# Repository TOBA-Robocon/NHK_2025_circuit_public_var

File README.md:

# 前提(注意)
USB-CのD+,D-にCANを流す異端ゲキヤバ思想。
USBに規格外信号を流すなって人はブラウザバックを推奨。
著作権保護とかのために本番で使ったデータをちょっと改変してたりする。

# 各基板説明

## CAN_HUB_SMD
USB-CのCANバスを分岐するための基板。

付属のXT60に給電することで分岐先のUSB-Cの電源ラインに電源を供給できる。

電源を供給することで後述する「偽C610(C810)」を駆動させることができる。

本番で使った基板にはれな子のシルクが乗っているため、部内では「れな子」と呼ばれていた。

## CANはぶ
CAN_HUB_SMDの旧バージョン。

使ってるUSB-Cのコネクタが違う。

## GOD_DC_MD
強いモタドラ

定格:40V/60A

## Next_main_Control
メインの基板。

ESP32とF405RGTがついている。Dualshock4の値をESP32で受け取ってCANバスに流し散らかす。

Dualshock4の値を使って各機構の処理をし、4本のUSB-C_CANで各基板にデータを転送する。

ESP32で流すデータの種類とか規格は「ESP32」フォルダの中を参照のこと。

## mecanum_HUB
メカナムを動かしている基板

CAN*1、ロリコン*2(XAコネクタ5pin)、リミットスイッチ*2(XAコネクタ2pin)、電流センサ*2、「GOD_DC_MD」を刺すスロット*2,

メイン基板からのデューティー比と回転方向司令をCANで受けてメカナムを回す

## ガチ夫
ベル直道機構をPID制御する基板

定格:40V/20A

CAN*1、ロリコン*1(XAコネクタ5pin)、リミットスイッチ*1(PHコネクタ2pin)、電流センサ*1、モータードライバ*1ch

メイン基板から速度司令をCANで受けて定速度でベル直を回す。

## 偽C610(C810)
C610サイズのDCモータードライバ

定格:24V/5A

USB-Cから電源とCANを引ける

CAN*1、リミットスイッチ*1(PHコネクタ2pin)、モータードライバ*1ch

メイン基板からデューティー比と回転方向司令をCANで受けてモーターを回す。

基板をロボットに固定するのがめんどくさすぎる駄作。

# iocs
各基板に乗っているSTM32用の.iocファイル群

参考程度にCubeIDE等で使って、どうぞ。

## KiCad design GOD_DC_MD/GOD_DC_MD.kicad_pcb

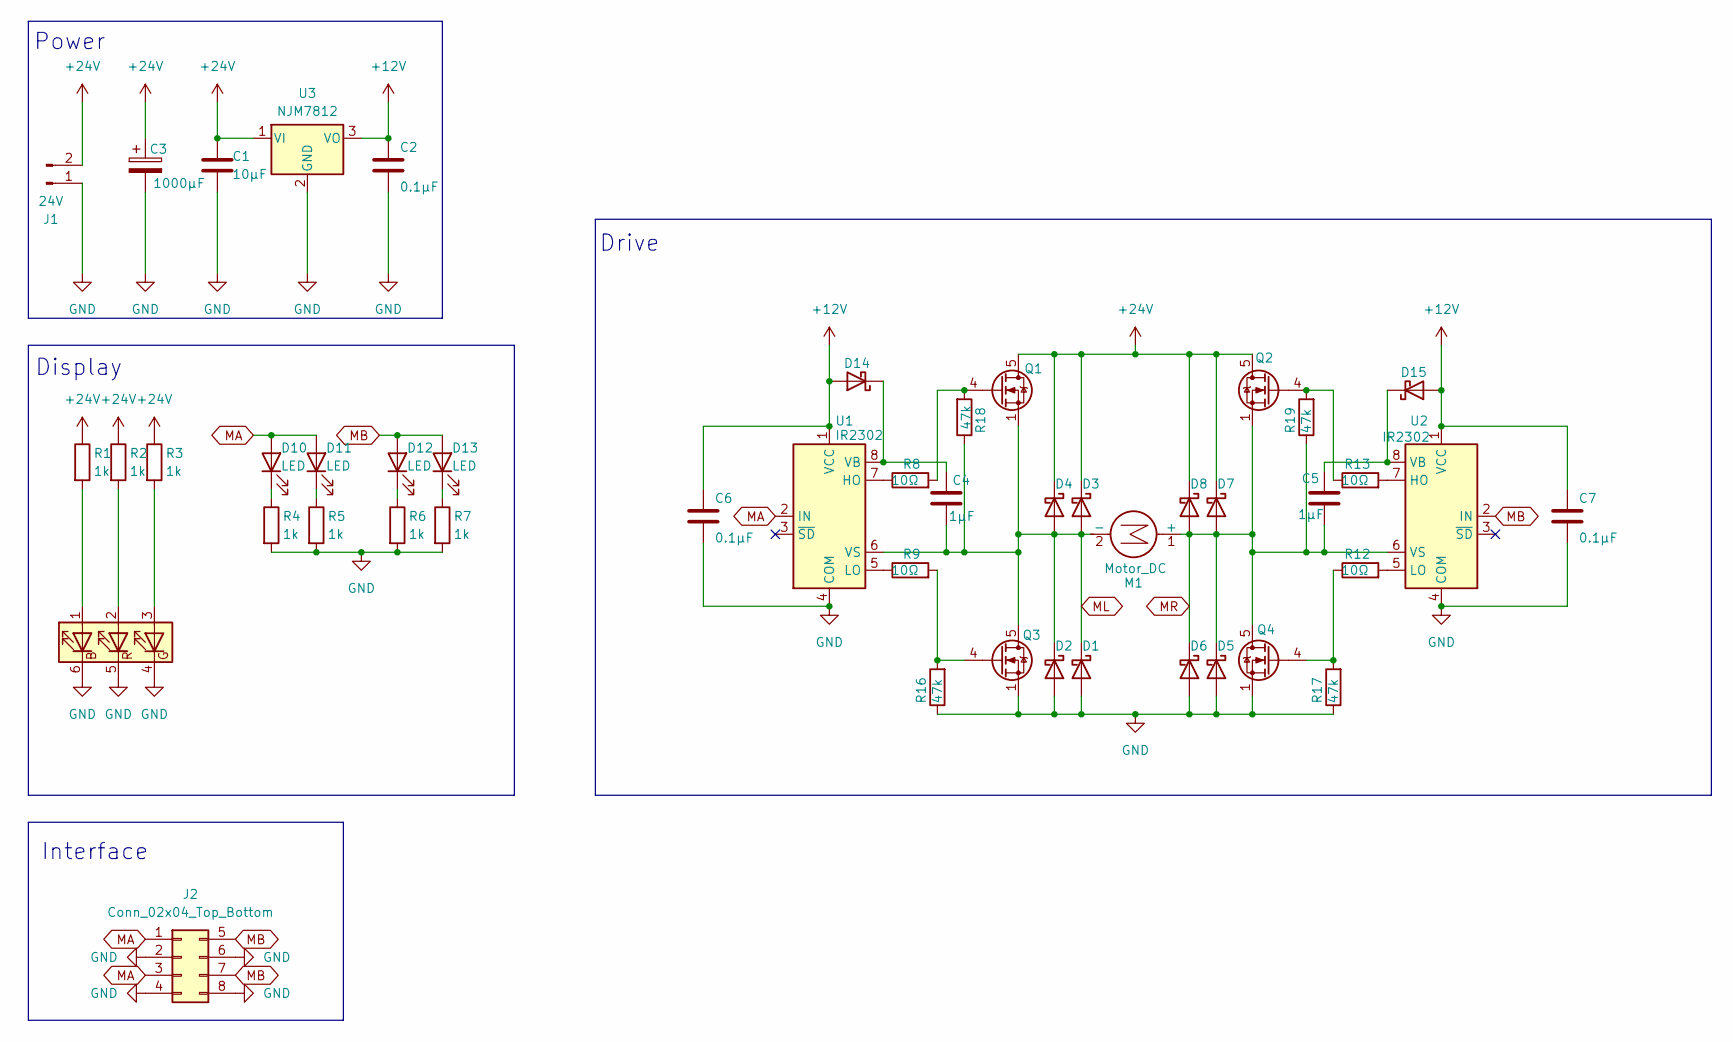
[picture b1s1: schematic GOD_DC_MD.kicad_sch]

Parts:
C1: 10μF; C_0603_1608Metric_Pad1.08x0.95mm_HandSolder
C2, C6, C7: 0.1μF; C_0603_1608Metric_Pad1.08x0.95mm_HandSolder
C3: 1000μF; CP_Radial_D10.0mm_P7.50mm
C4, C5: 1μF; C_0603_1608Metric_Pad1.08x0.95mm_HandSolder
D1, D2, D3, D4, D5, D6, D7, D8, D14, D15: SS14; D_SMA_Handsoldering
D9: SMLVN6RGB; LED_ROHM_SMLVN6
D10, D11, D12, D13: LED; LED_0603_1608Metric_Pad1.05x0.95mm_HandSolder
J1: 24V; AMASS_XT60PW-M_1x02_P7.20mm_Horizontal
J2: Conn_02x04_Top_Bottom; PinHeader_2x04_P2.54mm_Horizontal
M1: Motor_DC; AMASS_XT60PW-F_1x02_P7.20mm_Horizontal
Q1, Q2, Q3, Q4: BSC159N10LSFG; TDSON-8-1
R1, R2, R3, R4, R5, R6, R7: 1k; R_0603_1608Metric_Pad0.98x0.95mm_HandSolder
R8, R9, R12, R13: 10Ω; R_0603_1608Metric_Pad0.98x0.95mm_HandSolder
R16, R17, R18, R19: 47k; R_0603_1608Metric_Pad0.98x0.95mm_HandSolder
U1, U2: IR2302; SOIC-8_3.9x4.9mm_P1.27mm
U3: NJM7812; TO-252-2

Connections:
+12V: C2.1, C6.1, C7.1, D14.2 (A), D15.2 (A), U1.1 (VCC), U2.1 (VCC), U3.3 (VO)
+24V: C1.1, C3.1, D3.1 (K), D4.1 (K), D7.1 (K), D8.1 (K), J1.2, Q1.5 (D), Q2.5 (D), R1.1, R2.1, R3.1, U3.1 (VI)
GND: C1.2, C2.2, C3.2, C6.2, C7.2, D1.2 (A), D2.2 (A), D5.2 (A), D6.2 (A), D9.4 (GK), D9.5 (RK), D9.6 (BK), J1.1, J2.2, J2.4, J2.6, J2.8, Q3.1 (S), Q3.2 (S), Q3.3 (S), Q4.1 (S), Q4.2 (S), Q4.3 (S), R4.2, R5.2, R6.2, R7.2, R16.1, R17.1, U1.4 (COM), U2.4 (COM), U3.2 (GND)
MA: D10.2 (A), D11.2 (A), J2.1, J2.3, U1.2 (IN)
MB: D12.2 (A), D13.2 (A), J2.5, J2.7, U2.2 (IN)
ML: C4.2, D1.1 (K), D2.1 (K), D3.2 (A), D4.2 (A), M1.2 (-), Q1.1 (S), Q1.2 (S), Q1.3 (S), Q3.5 (D), R18.1, U1.6 (VS)
MR: C5.2, D5.1 (K), D6.1 (K), D7.2 (A), D8.2 (A), M1.1 (+), Q2.1 (S), Q2.2 (S), Q2.3 (S), Q4.5 (D), R19.1, U2.6 (VS)
unnamed: D9.1 (BA), R1.2
unnamed: D9.3 (GA), R3.2
unnamed: D9.2 (RA), R2.2
unnamed: D10.1 (K), R4.1
unnamed: D11.1 (K), R5.1
unnamed: D12.1 (K), R6.1
unnamed: D13.1 (K), R7.1
unnamed: C4.1, D14.1 (K), U1.8 (VB)
unnamed: C5.1, D15.1 (K), U2.8 (VB)
unnamed: Q1.4 (G), R8.2, R18.2
unnamed: Q2.4 (G), R13.1, R19.2
unnamed: Q3.4 (G), R9.2, R16.2
unnamed: Q4.4 (G), R12.1, R17.2
unnamed: R8.1, U1.7 (HO)
unnamed: R9.1, U1.5 (LO)
unnamed: R13.2, U2.7 (HO)
unnamed: R12.2, U2.5 (LO)

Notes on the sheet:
Display
Drive
Interface
Power

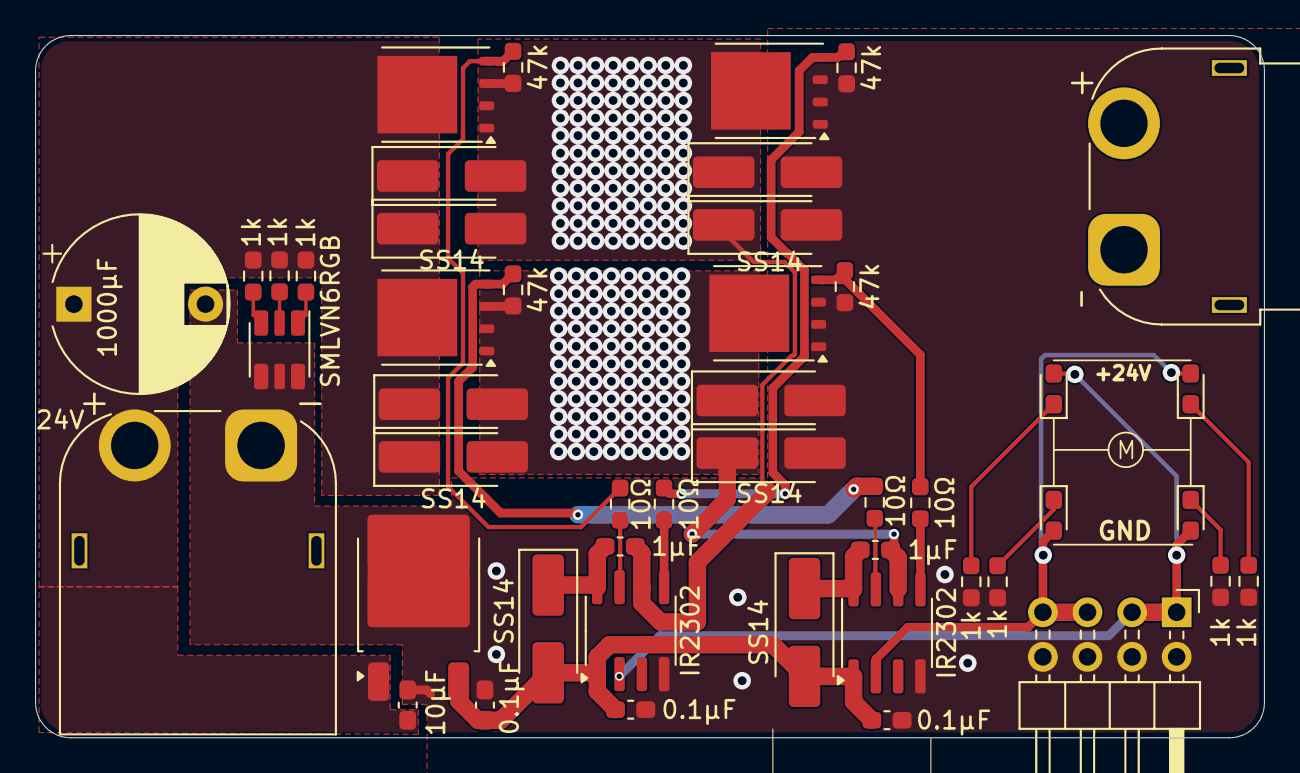
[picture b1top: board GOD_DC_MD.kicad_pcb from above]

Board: 2 copper layers, 70.0 x 40.0 mm, 47 parts (0 on the bottom side), 24 nets.

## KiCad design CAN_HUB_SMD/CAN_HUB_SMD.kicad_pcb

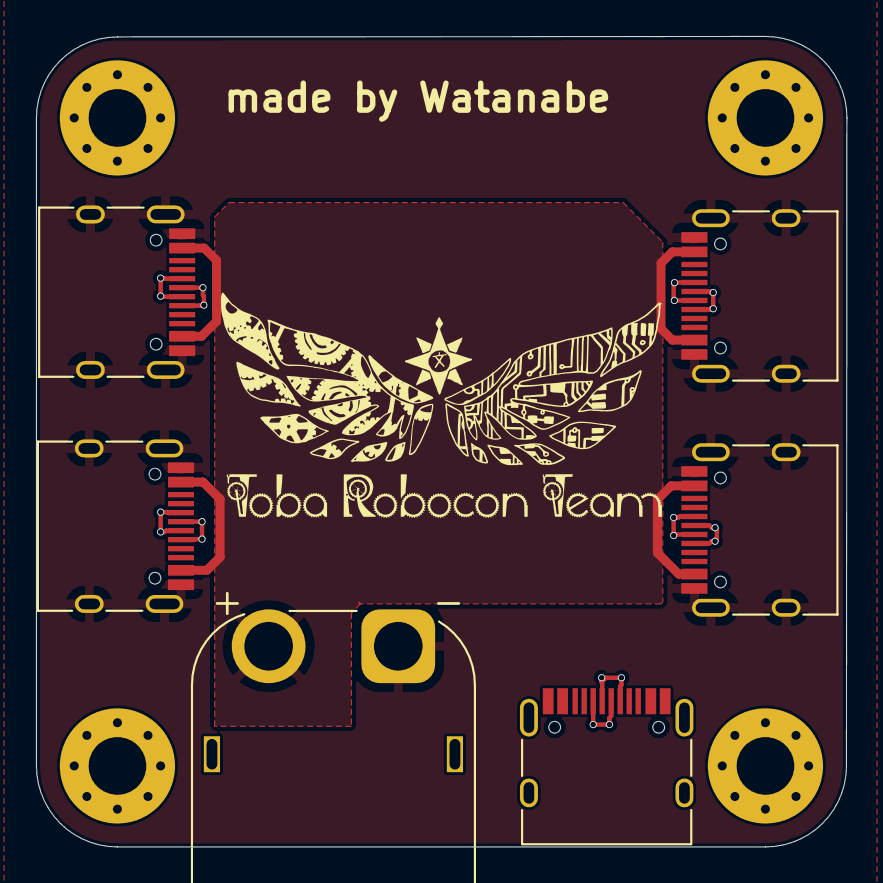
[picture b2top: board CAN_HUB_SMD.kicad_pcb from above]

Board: 2 copper layers, 45.0 x 45.0 mm, 10 parts (0 on the bottom side), 5 nets.

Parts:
H1, H2, H3, H4: MountingHole_Pad; MountingHole_3.2mm_M3_Pad_Via
J1: Conn_01x02_Pin; AMASS_XT60PW-M_1x02_P7.20mm_Horizontal
J2, J3, J4, J5, J6: USB_C_Receptacle_USB2.0_16P; USB_C_Receptacle_HRO_TYPE-C-31-M-12

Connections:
+24V: J1.2, J3.A4 (VBUS), J3.A9 (VBUS), J3.B4 (VBUS), J3.B9 (VBUS), J4.A4 (VBUS), J4.A9 (VBUS), J4.B4 (VBUS), J4.B9 (VBUS), J5.A4 (VBUS), J5.A9 (VBUS), J5.B4 (VBUS), J5.B9 (VBUS), J6.A4 (VBUS), J6.A9 (VBUS), J6.B4 (VBUS), J6.B9 (VBUS)
CAN_H: J2.A6 (D+), J2.B6 (D+), J3.A6 (D+), J3.B6 (D+), J4.A6 (D+), J4.B6 (D+), J5.A6 (D+), J5.B6 (D+), J6.A6 (D+), J6.B6 (D+)
CAN_L: J2.A7 (D-), J2.B7 (D-), J3.A7 (D-), J3.B7 (D-), J4.A7 (D-), J4.B7 (D-), J5.A7 (D-), J5.B7 (D-), J6.A7 (D-), J6.B7 (D-)
GND: J1.1, J3.A1 (GND), J3.A12 (GND), J3.B1 (GND), J3.B12 (GND), J3.S1 (SHIELD), J4.A1 (GND), J4.A12 (GND), J4.B1 (GND), J4.B12 (GND), J4.S1 (SHIELD), J5.A1 (GND), J5.A12 (GND), J5.B1 (GND), J5.B12 (GND), J5.S1 (SHIELD), J6.A1 (GND), J6.A12 (GND), J6.B1 (GND), J6.B12 (GND), J6.S1 (SHIELD)
unnamed: J2.A1 (GND), J2.A12 (GND), J2.B1 (GND), J2.B12 (GND)

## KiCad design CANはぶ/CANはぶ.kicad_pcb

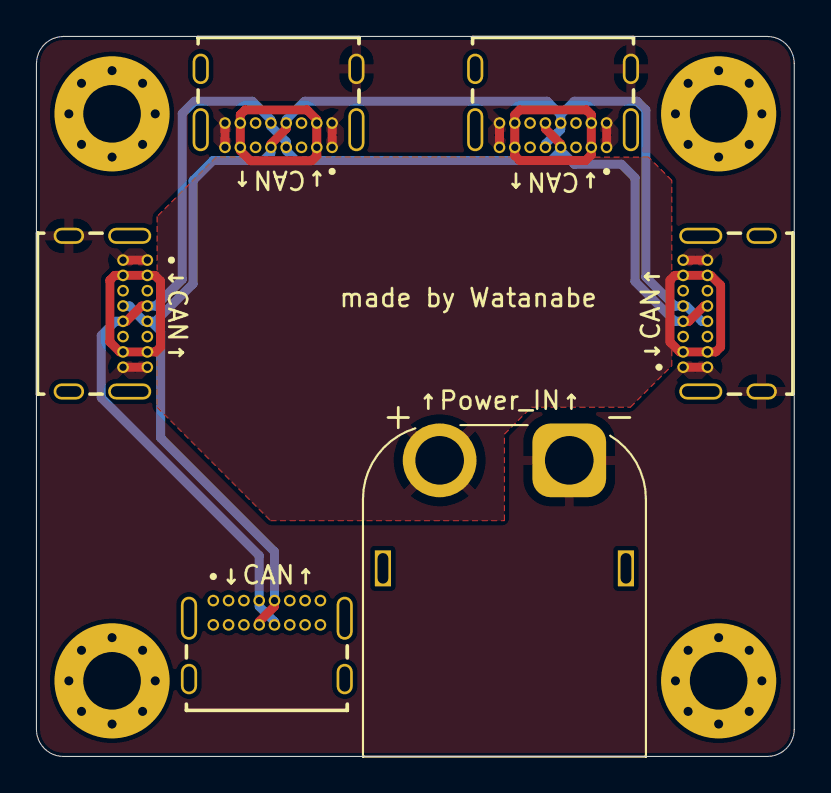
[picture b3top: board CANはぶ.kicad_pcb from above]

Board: 2 copper layers, 42.1 x 40.0 mm, 10 parts (0 on the bottom side), 4 nets.

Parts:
H1, H2, H3, H4: MountingHole_Pad; MountingHole_3.2mm_M3_Pad_Via
J1, J2, J3, J4, J5: USB_C_Receptacle_USB2.0_16P; GCT_USB4085-GF-A_REVB
J6: Conn_01x02_Pin; AMASS_XT60PW-M_1x02_P7.20mm_Horizontal

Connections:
+24V: J1.A4 (VBUS), J1.A9 (VBUS), J1.B4 (VBUS), J1.B9 (VBUS), J2.A4 (VBUS), J2.A9 (VBUS), J2.B4 (VBUS), J2.B9 (VBUS), J3.A4 (VBUS), J3.A9 (VBUS), J3.B4 (VBUS), J3.B9 (VBUS), J4.A4 (VBUS), J4.A9 (VBUS), J4.B4 (VBUS), J4.B9 (VBUS), J6.2
CAN_H: J1.A7 (D-), J1.B7 (D-), J2.A7 (D-), J2.B7 (D-), J3.A7 (D-), J3.B7 (D-), J4.A7 (D-), J4.B7 (D-), J5.A7 (D-), J5.B7 (D-)
CAN_L: J1.A6 (D+), J1.B6 (D+), J2.A6 (D+), J2.B6 (D+), J3.A6 (D+), J3.B6 (D+), J4.A6 (D+), J4.B6 (D+), J5.A6 (D+), J5.B6 (D+)
GND: J1.A1 (GND), J1.A12 (GND), J1.B1 (GND), J1.B12 (GND), J1.S1 (SHIELD), J2.A1 (GND), J2.A12 (GND), J2.B1 (GND), J2.B12 (GND), J2.S1 (SHIELD), J3.A1 (GND), J3.A12 (GND), J3.B1 (GND), J3.B12 (GND), J3.S1 (SHIELD), J4.A1 (GND), J4.A12 (GND), J4.B1 (GND), J4.B12 (GND), J4.S1 (SHIELD), J6.1

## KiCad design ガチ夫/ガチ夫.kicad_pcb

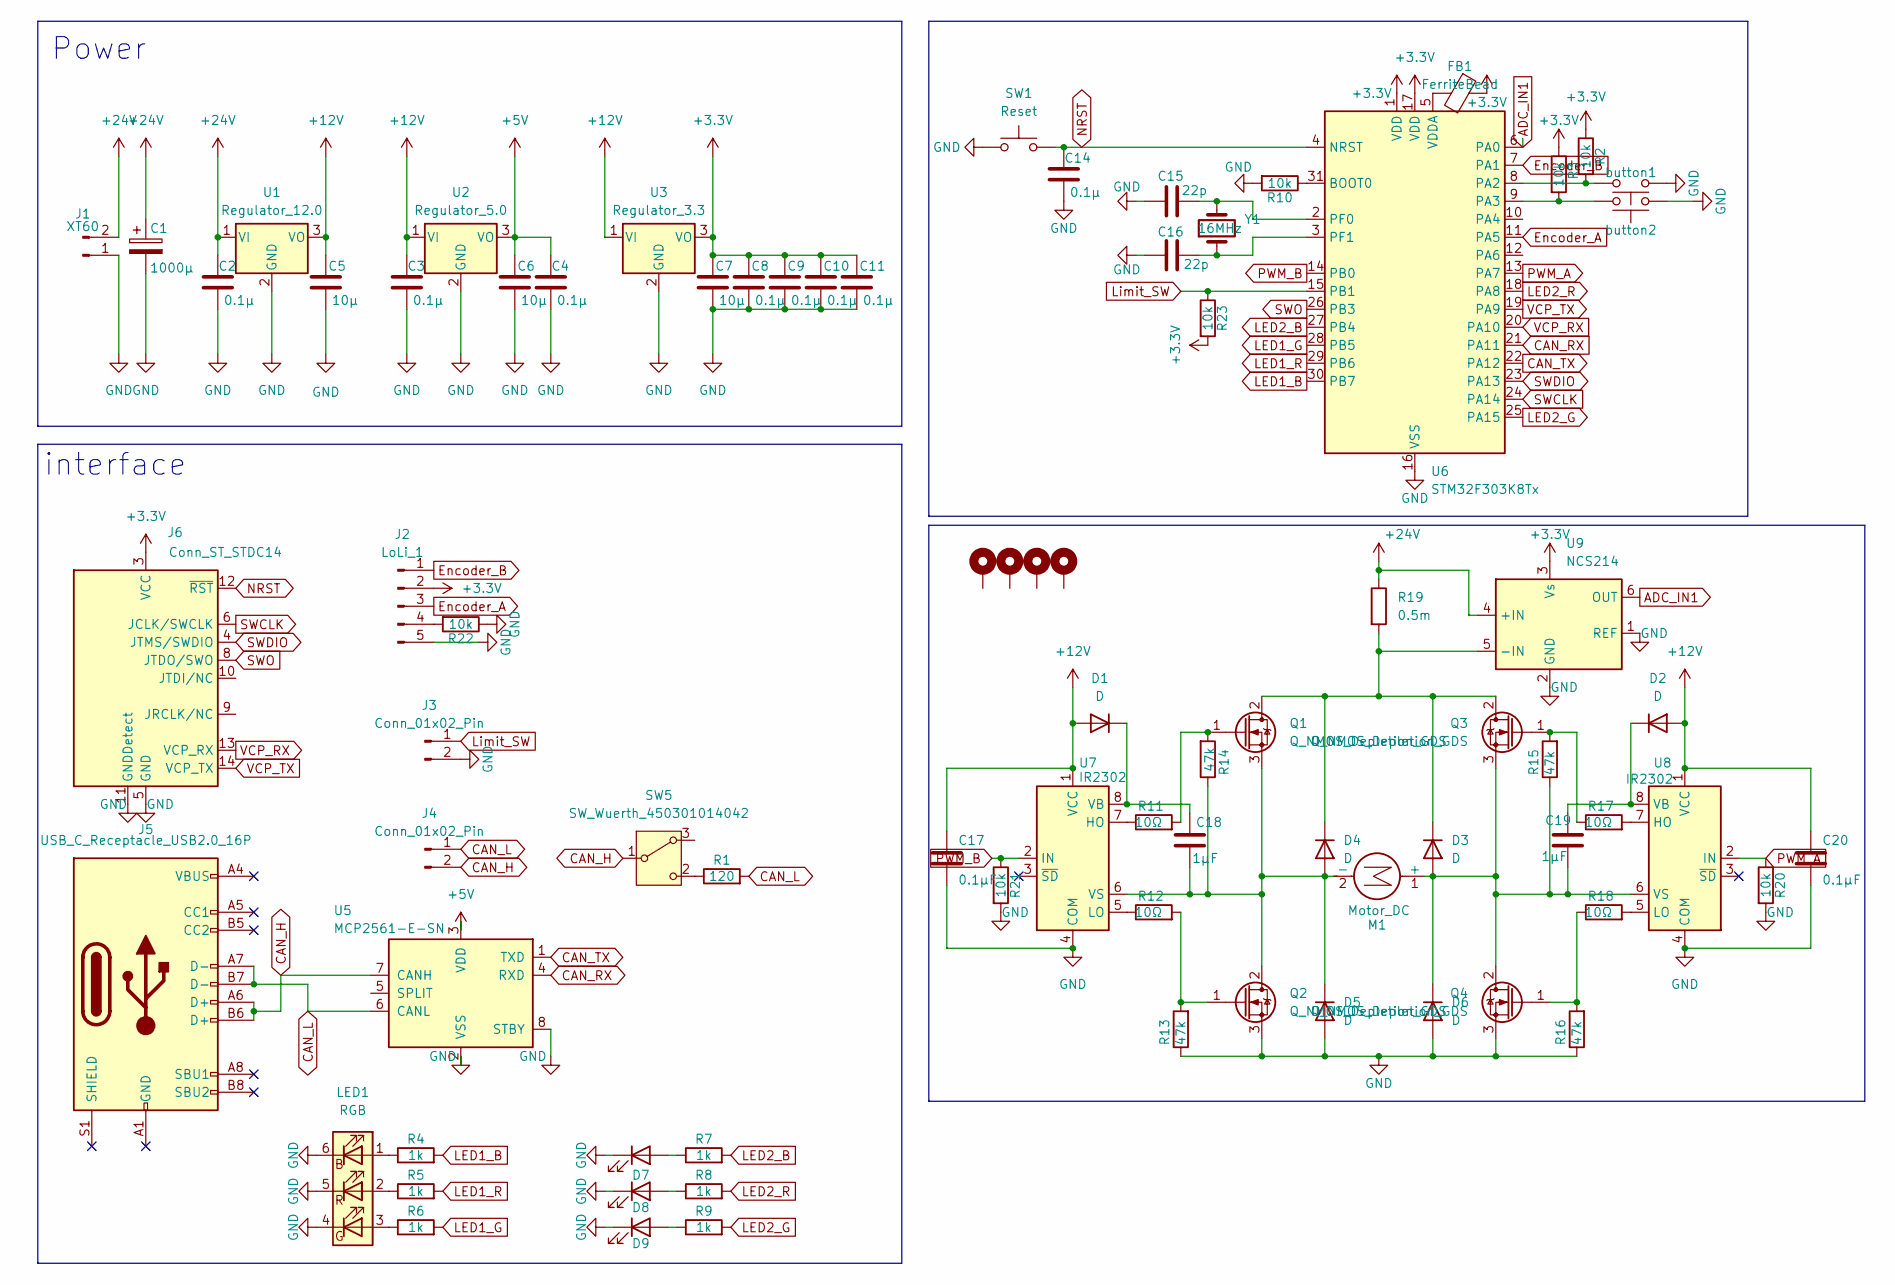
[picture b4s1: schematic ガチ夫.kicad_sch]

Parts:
C1: 1000μ; CP_Radial_D12.5mm_P5.00mm
C2, C3, C4, C8, C9, C10, C11, C14: 0.1μ; C_0603_1608Metric
C5, C6, C7: 10μ; C_0603_1608Metric
C15, C16: 22p; C_0603_1608Metric
C17, C20: 0.1μF; C_0603_1608Metric_Pad1.08x0.95mm_HandSolder
C18, C19: 1μF; C_0603_1608Metric_Pad1.08x0.95mm_HandSolder
D1, D2, D3, D4, D5, D6: D; D_SOD-123F
D7, D8, D9: LED; LED_0603_1608Metric
FB1: FerriteBead; L_0805_2012Metric_Pad1.05x1.20mm_HandSolder
H1, H2, H3, H4: MountingHole_Pad; MountingHole_3.2mm_M3_Pad_Via
J1: XT60; AMASS_XT60PW-M_1x02_P7.20mm_Horizontal
J2: LoLi_1; JST_XA_B05B-XASK-1_1x05_P2.50mm_Vertical
J3: Conn_01x02_Pin; JST_PH_B2B-PH-SM4-TB_1x02-1MP_P2.00mm_Vertical
J4: Conn_01x02_Pin; JST_XA_S02B-XASK-1N-BN_1x02_P2.50mm_Horizontal
J5: USB_C_Receptacle_USB2.0_16P; GCT_USB4085-GF-A_REVB
J6: Conn_ST_STDC14; PinHeader_2x07_P1.27mm_Vertical
LED1: RGB; LED_ROHM_SMLVN6
M1: Motor_DC; AMASS_XT60PW-F_1x02_P7.20mm_Horizontal
Q1, Q2, Q3, Q4: Q_NMOS_Depletion_GDS; TO-252-2
R1: 120; R_0603_1608Metric_Pad0.98x0.95mm_HandSolder
R2, R3, R10, R20, R21, R22, R23: 10k; R_0603_1608Metric
R4, R5, R6, R7, R8, R9: 1k; R_0603_1608Metric_Pad0.98x0.95mm_HandSolder
R11, R12, R17, R18: 10Ω; R_0603_1608Metric_Pad0.98x0.95mm_HandSolder
R13, R14, R15, R16: 47k; R_0603_1608Metric_Pad0.98x0.95mm_HandSolder
R19: 0.5m; R_2512_6332Metric
SW1: Reset; SW_PUSH_1P1T_6x3.5mm_H5.0_APEM_MJTP1250
SW3: button2; SW_PUSH_1P1T_6x3.5mm_H5.0_APEM_MJTP1250
SW4: button1; SW_PUSH_1P1T_6x3.5mm_H5.0_APEM_MJTP1250
SW5: SW_Wuerth_450301014042; SW_Slide-03_Wuerth-WS-SLTV_10x2.5x6.4_P2.54mm
U1: Regulator_12.0; TO-252-2
U2: Regulator_5.0; TO-252-2
U3: Regulator_3.3; TO-252-2
U5: MCP2561-E-SN; SOIC-8_3.9x4.9mm_P1.27mm
U6: STM32F303K8Tx; LQFP-32_7x7mm_P0.8mm
U7, U8: IR2302; SOIC-8_3.9x4.9mm_P1.27mm
U9: NCS214; SOT-363_SC-70-6_Handsoldering
Y1: 16MHz; Crystal_HC18-U_Vertical

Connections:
+3.3V: C7.1, C8.1, C9.1, C10.1, C11.1, FB1.1, J2.2, J6.3 (VCC), R2.1, R3.1, R23.2, U3.3 (VO), U6.1 (VDD), U6.17 (VDD), U9.3 (Vs)
+5V: C4.1, C6.1, U2.3 (VO), U5.3 (VDD)
+12V: C3.1, C5.1, C17.1, C20.1, D1.2 (A), D2.2 (A), U1.3 (VO), U2.1 (VI), U3.1 (VI), U7.1 (VCC), U8.1 (VCC)
+24V: C1.1, C2.1, J1.2, R19.1, U1.1 (VI), U9.4 (+IN)
ADC_IN1: U6.6 (PA0), U9.6 (OUT)
CAN_H: J4.2, J5.A6 (D+), J5.B6 (D+), SW5.1 (B), U5.7 (CANH)
CAN_L: J4.1, J5.A7 (D-), J5.B7 (D-), R1.2, U5.6 (CANL)
CAN_RX: U5.4 (RXD), U6.21 (PA11)
CAN_TX: U5.1 (TXD), U6.22 (PA12)
Encoder_A: J2.3, U6.11 (PA5)
Encoder_B: J2.1, U6.7 (PA1)
GND: C1.2, C2.2, C3.2, C4.2, C5.2, C6.2, C7.2, C8.2, C9.2, C10.2, C11.2, C14.2, C15.1, C16.1, C17.2, C20.2, D5.2 (A), D6.2 (A), D7.1 (K), D8.1 (K), D9.1 (K), J1.1, J2.5, J3.2, J6.5 (GND), J6.7 (GND), J6.11 (GNDDetect), LED1.4 (GK), LED1.5 (RK), LED1.6 (BK), Q2.3 (S), Q4.3 (S), R10.2, R13.1, R16.1, R20.2, R21.2, R22.1, SW1.1, SW3.1, SW4.1, U1.2 (GND), U2.2 (GND), U3.2 (GND), U5.2 (VSS), U5.8 (STBY), U6.16 (VSS), U6.32 (VSS), U7.4 (COM), U8.4 (COM), U9.1 (REF), U9.2 (GND)
LED1_B: R4.2, U6.30 (PB7)
LED1_G: R6.2, U6.28 (PB5)
LED1_R: R5.2, U6.29 (PB6)
LED2_B: R7.2, U6.27 (PB4)
LED2_G: R9.2, U6.25 (PA15)
LED2_R: R8.2, U6.18 (PA8)
Limit_SW: J3.1, R23.1, U6.15 (PB1)
NRST: C14.1, J6.12 (~RST), SW1.2, U6.4 (NRST)
unnamed: C18.1, D1.1 (K), U7.8 (VB)
unnamed: C19.1, D2.1 (K), U8.8 (VB)
unnamed: C19.2, D3.2 (A), D6.1 (K), M1.1 (+), Q3.3 (S), Q4.2 (D), R15.1, U8.6 (VS)
unnamed: D3.1 (K), D4.1 (K), Q1.2 (D), Q3.2 (D), R19.2, U9.5 (-IN)
unnamed: C18.2, D4.2 (A), D5.1 (K), M1.2 (-), Q1.3 (S), Q2.2 (D), R14.1, U7.6 (VS)
unnamed: D7.2 (A), R7.1
unnamed: D8.2 (A), R8.1
unnamed: D9.2 (A), R9.1
unnamed: J2.4, R22.2
unnamed: LED1.1 (BA), R4.1
unnamed: LED1.3 (GA), R6.1
unnamed: LED1.2 (RA), R5.1
unnamed: Q1.1 (G), R11.2, R14.2
unnamed: Q2.1 (G), R12.2, R13.2
unnamed: Q3.1 (G), R15.2, R17.1
unnamed: Q4.1 (G), R16.2, R18.1
unnamed: R1.1, SW5.2 (C)
unnamed: R10.1, U6.31 (BOOT0)
unnamed: R2.2, SW4.2, U6.8 (PA2)
unnamed: R3.2, SW3.2, U6.9 (PA3)
unnamed: C15.2, U6.2 (PF0), Y1.2
unnamed: C16.2, U6.3 (PF1), Y1.1
unnamed: FB1.2, U6.5 (VDDA)
unnamed: R11.1, U7.7 (HO)
unnamed: R12.1, U7.5 (LO)
unnamed: R17.2, U8.7 (HO)
unnamed: R18.2, U8.5 (LO)
PWM_A: R20.1, U6.13 (PA7), U8.2 (IN)
PWM_B: R21.1, U6.14 (PB0), U7.2 (IN)
SWCLK: J6.6 (JCLK/SWCLK), U6.24 (PA14)
SWDIO: J6.4 (JTMS/SWDIO), U6.23 (PA13)
SWO: J6.8 (JTDO/SWO), U6.26 (PB3)
VCP_RX: J6.13 (VCP_RX), U6.20 (PA10)
VCP_TX: J6.14 (VCP_TX), U6.19 (PA9)

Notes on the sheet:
interface
Power

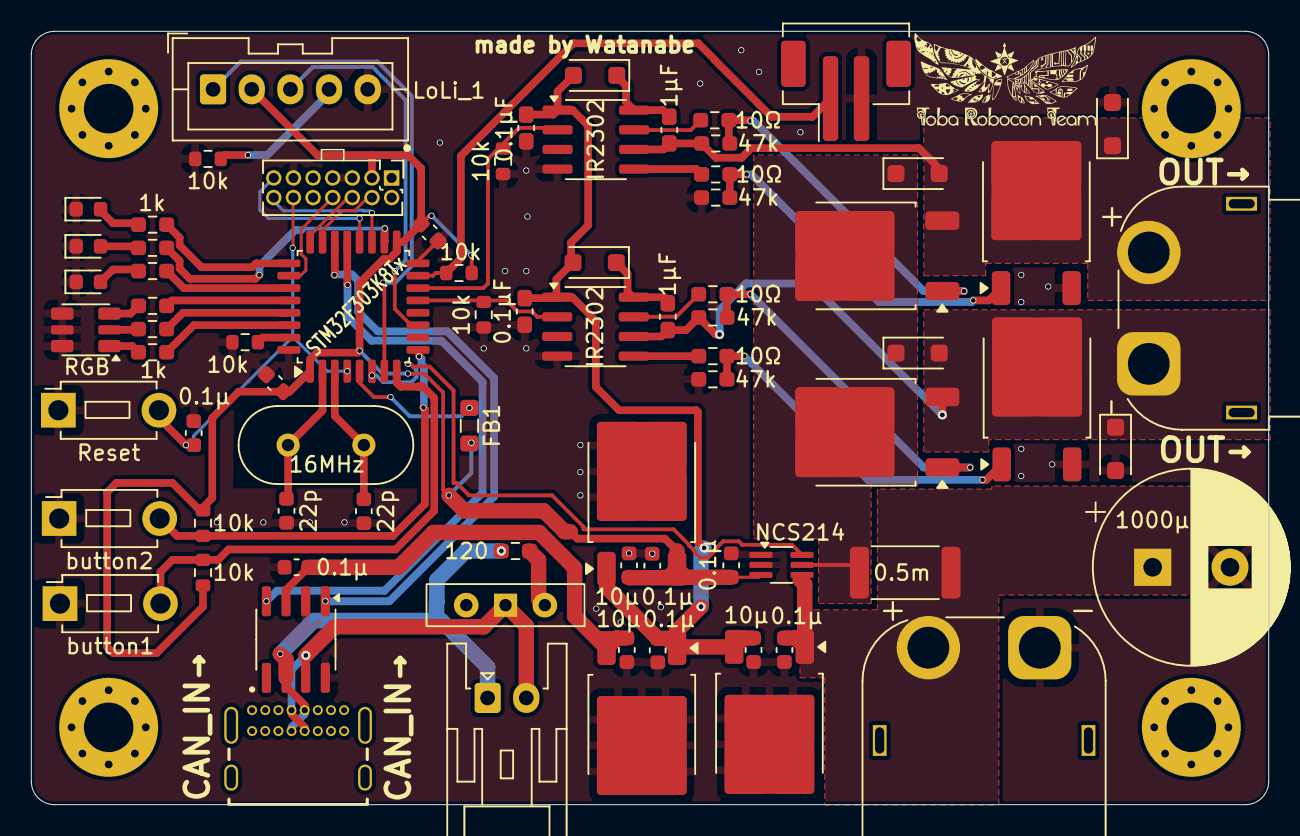
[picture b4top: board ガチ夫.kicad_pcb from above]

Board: 2 copper layers, 80.0 x 50.0 mm, 80 parts (0 on the bottom side), 54 nets.

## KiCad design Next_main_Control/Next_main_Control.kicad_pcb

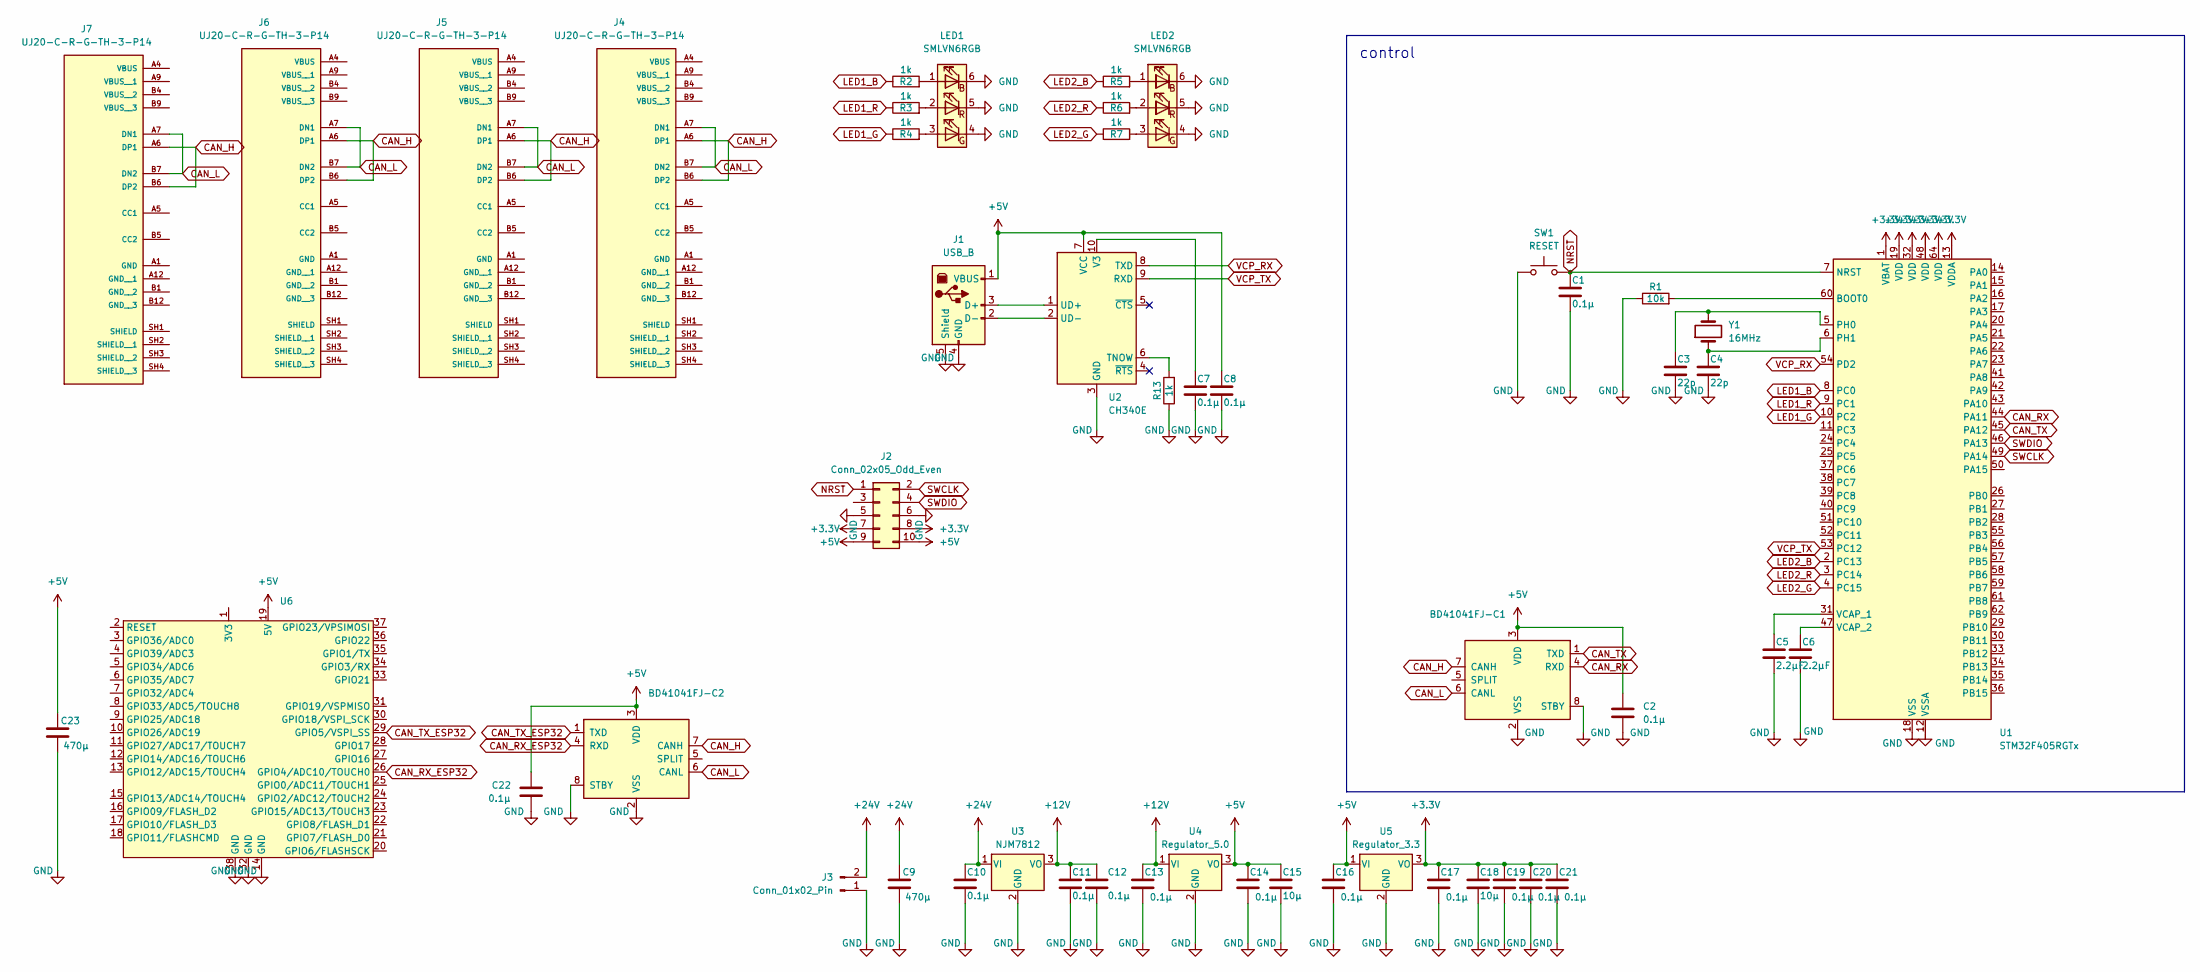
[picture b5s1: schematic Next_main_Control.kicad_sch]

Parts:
BD41041FJ-C1, BD41041FJ-C2: MCP2561-E-SN; SOIC-8_3.9x4.9mm_P1.27mm
C1, C2, C7, C8, C10, C11, C12, C13, C14, C16, C17, C19, C20, C21, C22: 0.1μ; C_0603_1608Metric_Pad1.08x0.95mm_HandSolder
C3, C4: 22p; C_0603_1608Metric_Pad1.08x0.95mm_HandSolder
C5, C6: 2.2μF; C_0603_1608Metric_Pad1.08x0.95mm_HandSolder
C9, C23: 470μ; CP_Radial_D8.0mm_P5.00mm
C15, C18: 10μ; C_0603_1608Metric_Pad1.08x0.95mm_HandSolder
J1: USB_B; USB_B_OST_USB-B1HSxx_Horizontal
J2: Conn_02x05_Odd_Even; IDC-Header_2x05_P2.54mm_Vertical
J3: Conn_01x02_Pin; AMASS_XT60PW-M_1x02_P7.20mm_Horizontal
J4, J5, J6, J7: UJ20-C-R-G-TH-3-P14; SAMESKY_UJ20-C-R-G-TH-3-P14; PARTREV 1.0
LED1, LED2: SMLVN6RGB; LED_ROHM_SMLVN6
R1: 10k; R_0603_1608Metric_Pad0.98x0.95mm_HandSolder
R2, R3, R4, R5, R6, R7, R13: 1k; R_0603_1608Metric_Pad0.98x0.95mm_HandSolder
SW1: RESET; SW_PUSH_6mm
U1: STM32F405RGTx; LQFP-64_10x10mm_P0.5mm
U2: CH340E; MSOP-10_3x3mm_P0.5mm
U3: NJM7812; TO-252-2
U4: Regulator_5.0; TO-252-2
U5: Regulator_3.3; TO-252-2
U6: ESP32_DevkitC
Y1: 16MHz; Crystal_HC18-U_Vertical

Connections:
+3.3V: C17.1, C18.1, C19.1, C20.1, C21.1, J2.7, J2.8, U1.1 (VBAT), U1.13 (VDDA), U1.19 (VDD), U1.32 (VDD), U1.48 (VDD), U1.64 (VDD), U5.3 (VO)
+5V: BD41041FJ-C1.3 (VDD), BD41041FJ-C2.3 (VDD), C2.1, C8.1, C14.1, C15.1, C16.1, C22.1, C23.1, J1.1 (VBUS), J2.9, J2.10, U2.7 (VCC), U4.3 (VO), U5.1 (VI), U6.19 (5V)
+12V: C11.1, C12.1, C13.1, U3.3 (VO), U4.1 (VI)
+24V: C9.1, C10.1, J3.2, U3.1 (VI)
CAN_H: BD41041FJ-C1.7 (CANH), BD41041FJ-C2.7 (CANH), J4.A6 (DP1), J4.B6 (DP2), J5.A6 (DP1), J5.B6 (DP2), J6.A6 (DP1), J6.B6 (DP2), J7.A6 (DP1), J7.B6 (DP2)
CAN_L: BD41041FJ-C1.6 (CANL), BD41041FJ-C2.6 (CANL), J4.A7 (DN1), J4.B7 (DN2), J5.A7 (DN1), J5.B7 (DN2), J6.A7 (DN1), J6.B7 (DN2), J7.A7 (DN1), J7.B7 (DN2)
CAN_RX: BD41041FJ-C1.4 (RXD), U1.44 (PA11)
CAN_RX_ESP32: BD41041FJ-C2.4 (RXD), U6.26 (GPIO4/ADC10/TOUCH0)
CAN_TX: BD41041FJ-C1.1 (TXD), U1.45 (PA12)
CAN_TX_ESP32: BD41041FJ-C2.1 (TXD), U6.29 (GPIO5/VSPI_SS)
GND: BD41041FJ-C1.2 (VSS), BD41041FJ-C1.8 (STBY), BD41041FJ-C2.2 (VSS), BD41041FJ-C2.8 (STBY), C1.2, C2.2, C3.2, C4.2, C5.2, C6.2, C7.2, C8.2, C9.2, C10.2, C11.2, C12.2, C13.2, C14.2, C15.2, C16.2, C17.2, C18.2, C19.2, C20.2, C21.2, C22.2, C23.2, J1.4 (GND), J1.5 (Shield), J2.5, J2.6, J3.1, LED1.4 (GK), LED1.5 (RK), LED1.6 (BK), LED2.4 (GK), LED2.5 (RK), LED2.6 (BK), R1.1, R13.1, SW1.1, U1.12 (VSSA), U1.18 (VSS), U1.63 (VSS), U2.3 (GND), U3.2 (GND), U4.2 (GND), U5.2 (GND), U6.14 (GND), U6.32 (GND), U6.38 (GND)
LED1_B: R2.1, U1.8 (PC0)
LED1_G: R4.1, U1.10 (PC2)
LED1_R: R3.1, U1.9 (PC1)
LED2_B: R5.1, U1.2 (PC13)
LED2_G: R7.1, U1.4 (PC15)
LED2_R: R6.1, U1.3 (PC14)
NRST: C1.1, J2.1, SW1.2, U1.7 (NRST)
unnamed: J1.3 (D+), U2.1 (UD+)
unnamed: J1.2 (D-), U2.2 (UD-)
unnamed: LED1.1 (BA), R2.2
unnamed: LED1.3 (GA), R4.2
unnamed: LED1.2 (RA), R3.2
unnamed: LED2.1 (BA), R5.2
unnamed: LED2.3 (GA), R7.2
unnamed: LED2.2 (RA), R6.2
unnamed: R1.2, U1.60 (BOOT0)
unnamed: C3.1, U1.5 (PH0), Y1.2
unnamed: C4.1, U1.6 (PH1), Y1.1
unnamed: C5.1, U1.31 (VCAP_1)
unnamed: C6.1, U1.47 (VCAP_2)
unnamed: R13.2, U2.6 (TNOW)
unnamed: C7.1, U2.10 (V3)
SWCLK: J2.2, U1.49 (PA14)
SWDIO: J2.4, U1.46 (PA13)
VCP_RX: U1.54 (PD2), U2.8 (TXD)
VCP_TX: U1.53 (PC12), U2.9 (RXD)

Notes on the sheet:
control

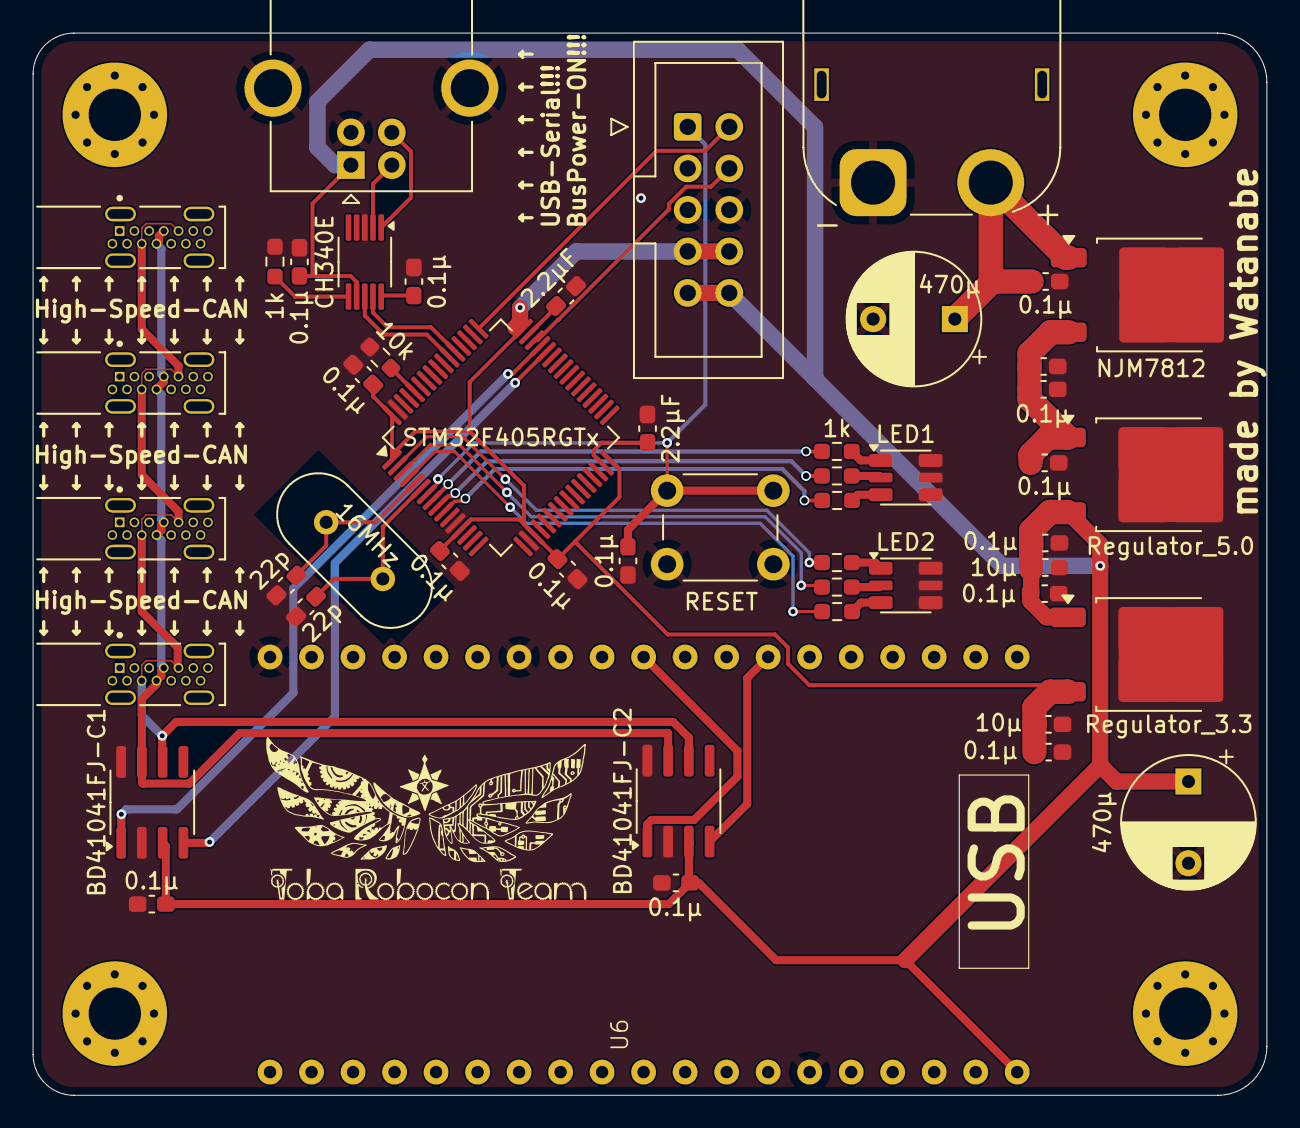
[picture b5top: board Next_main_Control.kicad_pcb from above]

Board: 2 copper layers, 75.5 x 65.0 mm, 50 parts (0 on the bottom side), 37 nets.
